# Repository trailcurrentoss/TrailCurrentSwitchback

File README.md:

# TrailCurrent Switchback

CAN-controlled 8-channel relay module for the TrailCurrent ecosystem, built on the [Waveshare ESP32-S3-ETH-8DI-8RO-C](https://www.waveshare.com/wiki/ESP32-S3-ETH-8DI-8RO-C).

## Hardware

For a full design overview see [DOCS/Requirements/high-level-requirements.md](DOCS/Requirements/high-level-requirements.md).

The Waveshare ESP32-S3-ETH-8DI-8RO-C provides:

- **ESP32-S3** dual-core LX7 @ 240 MHz with WiFi and BLE
- **8 relay channels** (1NO/1NC each), rated 10A @ 250V AC / 10A @ 30V DC, via TCA9554PWR I2C I/O expander
- **8 digital inputs** (optocoupler isolated)
- **CAN bus** with onboard transceiver and 120 ohm termination jumper
- **Ethernet** (W5500 via SPI, 10/100 Mbps)
- **7-36V DC** input (or 5V via USB-C)
- **RTC** (PCF85063ATL) with battery backup header
- **SD card** slot (MMC 1-bit mode)
- DIN-rail mount enclosure

## Firmware

### Pin Assignments

Relays are controlled via TCA9554PWR I2C I/O expander (address 0x20) on I2C SDA=GPIO42, SCL=GPIO41.

| Function   | Pin / Address |
|------------|---------------|
| Relay 1-8  | TCA9554 P0-P7 (I2C 0x20) |
| DI 1-8     | GPIO 4-11     |
| CAN TX     | GPIO 17       |
| CAN RX     | GPIO 18       |
| Buzzer     | GPIO 46       |
| RGB LED    | GPIO 38       |
| ETH MOSI   | GPIO 13       |
| ETH MISO   | GPIO 14       |
| ETH SCLK   | GPIO 15       |
| ETH CS     | GPIO 16       |

### CAN Protocol

CAN bus runs at **500 kbps** in no-ACK mode.

| CAN ID | Direction | Description |
|--------|-----------|-------------|
| `0x00` | RX | **OTA trigger** — 3-byte payload (MAC bytes 3-5) targets a specific device |
| `0x01` | RX | **WiFi config** — multi-message chunked protocol to provision SSID and password |
| `0x12 + addr` | TX | **Digital input broadcast** — 2-byte Picket-format frame (byte 0 = DI1-DI8 bitmask, byte 1 = 0x00), 5 Hz. Identical wire format to `PicketStatus0..7`, so Headwaters decodes it through the same path. |
| `0x25 + addr` | RX | **Relay toggle** — toggle a single relay (channel 0-7) or set all relays (channel >= 8, byte 2 = on/off) |
| `0x28 + addr` | TX | **Relay status broadcast** — 1-byte bitmask (bits 0-7 = relay states), sent at ~30 Hz |

Up to 3 Switchback modules can share the same CAN bus. CAN IDs are offset by the `SWITCHBACK_ADDRESS` build flag:

| Base ID | Addr 0 | Addr 1 | Addr 2 | Description |
|---------|--------|--------|--------|-------------|
| 0x12 | 0x12 | 0x13 | 0x14 | Digital input broadcast (TX) — `PicketStatus8/9/10` |
| 0x25 | 0x25 | 0x26 | 0x27 | Relay toggle (RX) |
| 0x28 | 0x28 | 0x29 | 0x2A | Relay status broadcast (TX) |

The DI broadcast (CAN ID `0x12 + addr`) reuses the **Picket** message format byte-for-byte: byte 0 carries DI1-DI8 (`1` = open / no current through optocoupler, `0` = closed); byte 1 is always `0x00` (Picket uses it for inputs 9-12, which Switchback hardware doesn't expose). Inputs are debounced for 50 ms and the frame is sent at 5 Hz, matching Picket exactly. For dry-contact wiring, connect each NO reed switch between its `DIn` terminal and `DGND` — the board's internal isolated rail biases the optocoupler LEDs, so no external supply is needed. See [DOCS/switchback-pinout.png](DOCS/switchback-pinout.png) for the full wiring diagram.

### WiFi Provisioning over CAN

WiFi credentials can be sent to the device over the CAN bus using a multi-message protocol on CAN ID `0x01`:

1. **Start** (type `0x01`) — declares SSID length, password length, chunk counts, and checksum
2. **SSID chunks** (type `0x02`) — up to 6 bytes per message, indexed
3. **Password chunks** (type `0x03`) — up to 6 bytes per message, indexed
4. **End** (type `0x04`) — verifies XOR checksum and saves credentials to NVS

A 5-second timeout resets the state if the sequence is not completed.

### OTA Updates

The firmware supports over-the-air updates via WiFi. An OTA trigger message on CAN ID `0x00` with the device's MAC address (bytes 3-5) puts the device into OTA mode. The flash partition table supports dual-OTA (app0/app1) for safe rollback.

Always use the app-only binary (`switchback_addr{N}.bin`) for OTA, never the merged binary. The merged binary starts with the bootloader, not an app header, and would fail the `esp_ota_end` validation.

```bash
curl -X POST http://esp32-XXYYZZ.local/ota --data-binary @build/switchback_addr0.bin
```

## Building

### Prerequisites

- [ESP-IDF](https://docs.espressif.com/projects/esp-idf/en/stable/esp32s3/get-started/) v5.x

### Build and Flash

```bash
idf.py set-target esp32s3
idf.py build
idf.py -p /dev/ttyACM0 flash monitor
```

### Multi-Instance Addressing

Up to 3 Switchback modules can share the same CAN bus. Each module is built with a unique address:

```bash
idf.py build                        # Address 0 (default)
idf.py build -DSWITCHBACK_ADDRESS=1  # Address 1
idf.py build -DSWITCHBACK_ADDRESS=2  # Address 2
```

#### Building All Variants

Use `build-all.sh` to build all 3 address variants in a single run:

```bash
./build-all.sh
```

This produces two binaries per address — one for OTA updates, one for the web flasher:

| File | Contents | Used By |
|------|----------|---------|
| `build/switchback_addr{N}.bin` | Application image only | Headwaters OTA (`deploy.sh`, `ota.js`), direct `curl` uploads |
| `build/switchback_addr{N}_merged.bin` | Bootloader + partition table + OTA data + application | Web flasher (full flash at 0x0) |

The two binary types exist because OTA and the web flasher write to different targets. Headwaters OTA sends the binary to the device's `/ota` HTTP endpoint, which calls `esp_ota_write` to write it to a single app partition. That function validates the image as an application — a merged binary starts with the bootloader instead of an app header, so it would fail validation. The web flasher writes the entire flash contents starting at offset 0x0, so it needs all partitions combined into one file.

#### Creating a GitHub Release

After building all variants, attach all 6 binaries (3 app-only + 3 merged) as release assets:

```bash
git tag -a v1.0.0 -m "Firmware release v1.0.0"
git push origin v1.0.0

gh release create v1.0.0 \
  build/switchback_addr0.bin \
  build/switchback_addr1.bin \
  build/switchback_addr2.bin \
  build/switchback_addr0_merged.bin \
  build/switchback_addr1_merged.bin \
  build/switchback_addr2_merged.bin \
  --repo trailcurrentoss/TrailCurrentSwitchback \
  --title "v1.0.0" \
  --notes "Firmware release v1.0.0"
```

Both the Headwaters deployment system and the web flasher pull from GitHub releases. The web flasher matches `_merged.bin` files by name for full-flash use. The Headwaters deployment system (`fetch-firmware.sh`) downloads the app-only `switchback_addr{N}.bin` files for OTA delivery.

## Project Structure

```
TrailCurrentSwitchback/
├── main/
│   ├── main.c              # Entry point — init and CAN task
│   ├── board.h             # Pin definitions for ESP32-S3-ETH-8DI-8RO-C
│   ├── relay.h / relay.c   # TCA9554 I2C relay driver (8 channels)
│   ├── can_handler.h / .c  # CAN protocol and message handling
│   ├── wifi_config.h / .c  # WiFi credential storage and CAN provisioning
│   ├── discovery.h / .c    # mDNS self-discovery and Headwaters registration
│   └── ota.h / ota.c       # OTA firmware updates via WiFi
├── CMakeLists.txt          # Top-level ESP-IDF project file
├── partitions.csv          # Custom flash partition table (dual OTA)
├── build-all.sh            # Build all 3 address variants (addr 0-2)
└── sdkconfig.defaults      # Default SDK configuration
```

## License

See [LICENSE](LICENSE) for details.

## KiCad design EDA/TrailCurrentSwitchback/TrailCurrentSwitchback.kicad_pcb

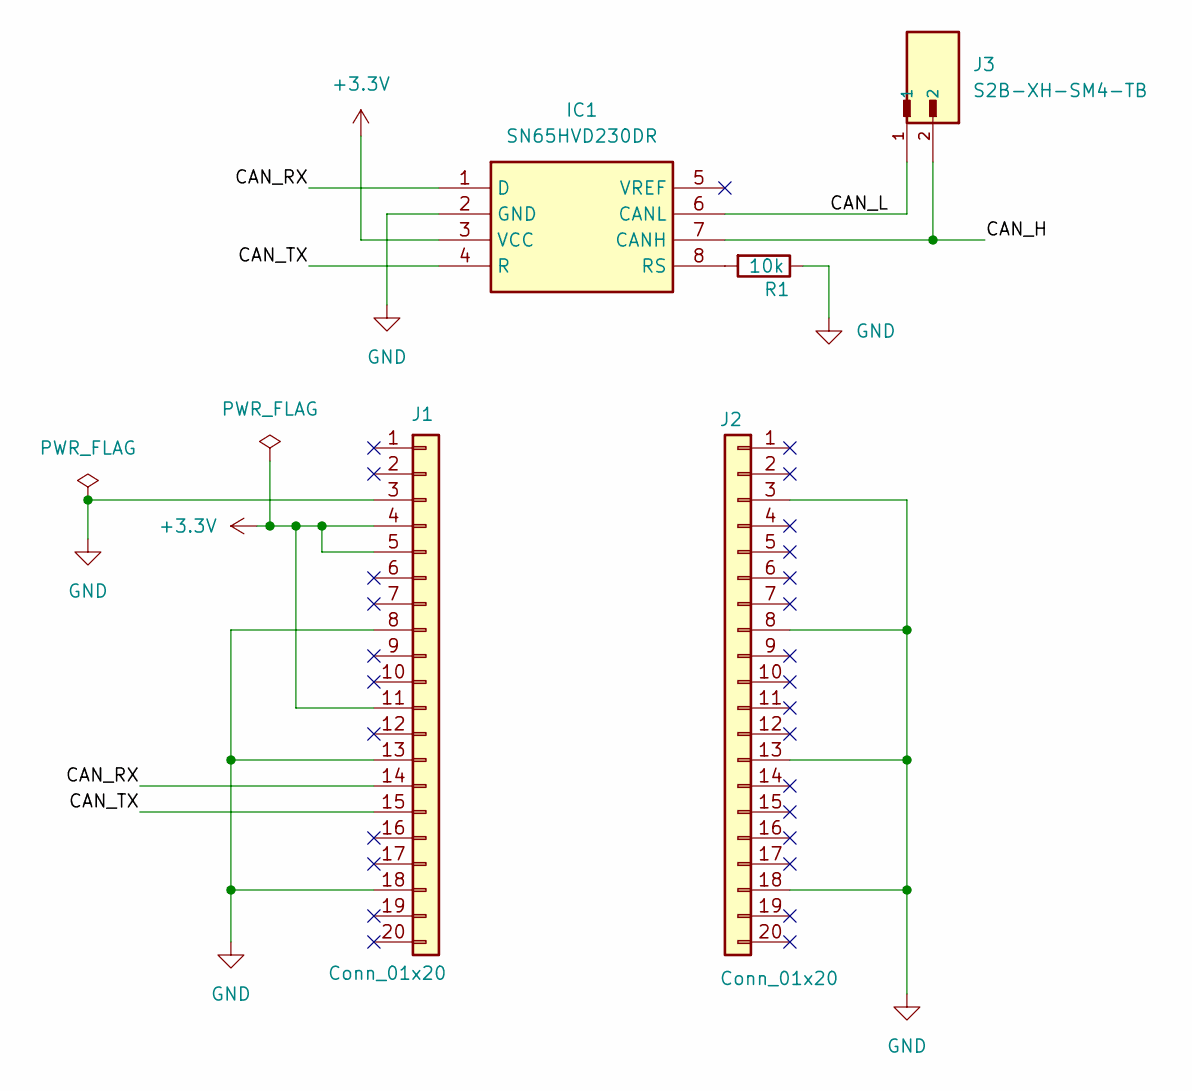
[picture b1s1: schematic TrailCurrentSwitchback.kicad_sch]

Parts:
IC1: SN65HVD230DR; Mouser Part Number 595-SN65HVD230DR
J1, J2: Conn_01x20; PinSocket_1x20_P2.54mm_Vertical
J3: S2B-XH-SM4-TB; JST_S2B-XH-SM4-TB
R1: 10k; R_1206_3216Metric_Pad1.30x1.75mm_HandSolder

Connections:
+3.3V: IC1.3 (VCC), J1.4, J1.5, J1.11
/CAN_H: IC1.7 (CANH), J3.2
/CAN_L: IC1.6 (CANL), J3.1
/CAN_RX: IC1.1 (D), J1.14
/CAN_TX: IC1.4 (R), J1.15
GND: IC1.2 (GND), J1.3, J1.8, J1.13, J1.18, J2.3, J2.8, J2.13, J2.18, R1.1
unnamed: IC1.8 (RS), R1.2

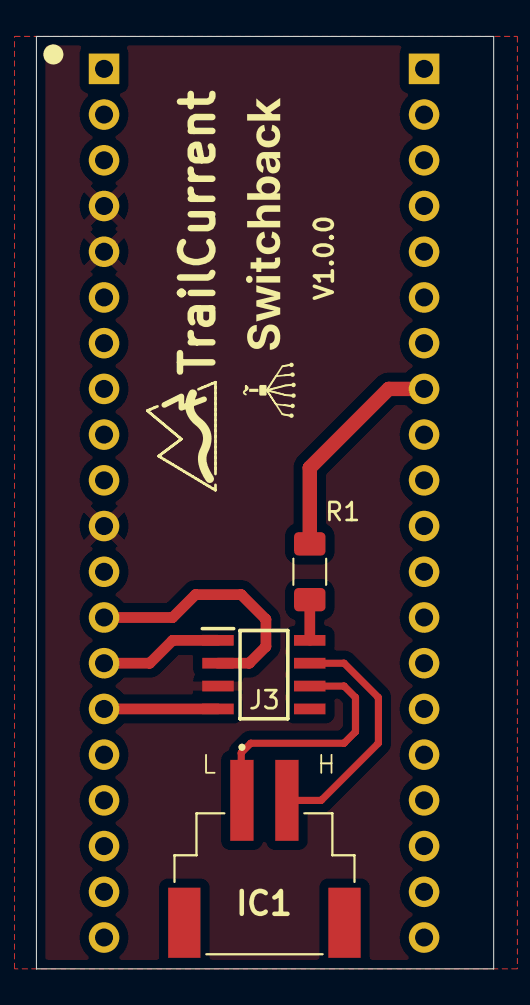
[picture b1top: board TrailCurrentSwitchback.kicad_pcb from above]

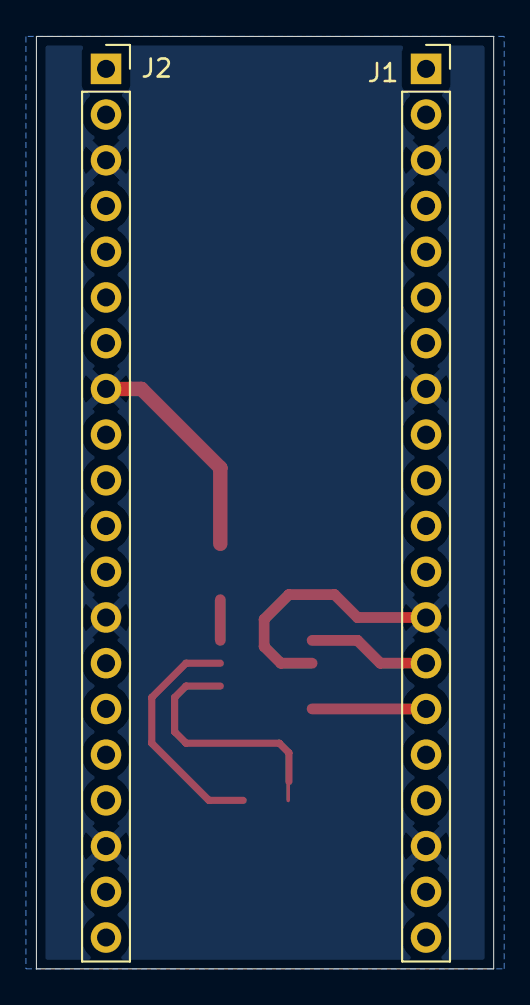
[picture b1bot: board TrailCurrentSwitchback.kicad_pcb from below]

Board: 2 copper layers, 25.4 x 51.8 mm, 7 parts (2 on the bottom side), 7 nets.

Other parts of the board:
LOGO: TrailCurrentLogo_Icon
LOGO#2: TrailCurrentLogo_Text

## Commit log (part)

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2026-03-11 Starting project
2026-03-11 Adding EDA, currently empty will populate for hat soon.
2026-03-11 Adding readme
2026-03-11 EDA for CAN Hat for waveshare relay and cad for milling pcb edges and drilling holes on Genmitsu 3030
2026-03-11 Updated EDA for professional assembly. Gerber files added ordered 1.0.0 version of the PCB for testing.
2026-03-12 Updates to CAD for paths
2026-03-15 Updated library fixes
2026-03-26 Migrated to ESP-IDF
2026-03-26 Updated sdkconfig
2026-03-26 Updated documentation
2026-03-26 Updates to handle CAN scenarios better and let nodes join and leave as needed
2026-03-27 Validated initial handshake for discovery
2026-03-27 Adding project version so discovery shows it.
2026-03-28 Fixed bug where discovery would disrupt CAN messaging
2026-03-28 Implement OTA firmware update via HTTP POST /ota endpoint
    Replace stubbed OTA trigger handler with full implementation matching
    sibling projects. Device enters OTA mode on CAN ID 0x00, connects WiFi,
    exposes HTTP server for firmware upload, and reboots on success.
    Includes mutual exclusion with discovery mode.
2026-03-28 Fixing issue with CAN Bus stops responding when discovery happens
2026-04-09 Updated to build all address combinations for switchback
2026-04-09 Fixed merged binaries for releasese
2026-04-09 Fixes for I2C timeouts
2026-04-10 Updated build script and documentation to reflect all the binaries needed for both web flash and OTA.
2026-04-15 Test release
2026-04-15 Testing versioning
2026-04-15 Moving to central CAN library
2026-04-15 Fixing flash and psram sizes
2026-05-10 Added picket messaging using the Digital inputs of the waveshare device
2026-06-21 Added logging for picket states and fixed flash issue with build-all
